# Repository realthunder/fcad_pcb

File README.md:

## FreeCAD scripts for PCB CAD/CAM & FEM

fcad_pcb is yet another way to improve ECAD/MCAD collaboration between
[FreeCAD](https://www.freecad.org/) and [KiCAD](https://kicad.org/).

The original purpose of these tools was to do **PCB milling in FreeCAD**. It can do much more now.:
* It can **generate gcode from kicad_pcb** directly without going through the gerber stage.
* It can let your **modify the PCB directly inside FC** (done already),
* and potentially export back to kicad_pcb (partially done).
* and finally it can **generate solid tracks, pads and plated drills to enable FEM and thermal analysis** on KiCad pcb boards.

## Installation

The fcad_pcb macro is written in Python and requires **FreeCAD 0.17** or later to work properly.

1. Clone this repo into your freecad macro directory. To check what the default path of your macro directory is go to dropdown `Macro` > `Macros..` and find the path in the field User macros location
    ```bash
    cd <path/to/your/macros/directory>
    git clone https://github.com/realthunder/fcad_pcb/
    ```
2. Enter the locally cloned repository
    ```bash
    cd fcad_pcb/
    ``` 
3. Download the repository submodules
    ```python
    git submodule update --init --recursive
    ```
4. Restart FreeCAD

## Usage

At this time fcad is usable through the [FreeCAD python console](https://wiki.freecad.org/Python_console). 

* Start FreeCAD,
* Launch the python console
  Enable through the `View > Panels > Python Console` dropdown menu
* Invoke the python `import` command to load fcad_pcb:
  ```python
  from fcad_pcb import kicad
  ```
**Result:** you are now ready to use fcad_pcb. 

#### Generating copper layers

```python
from fcad_pcb import kicad
pcb = kicad.KicadFcad(<full_path_to_your_kicad_pcb_file>)
pcb.makeCoppers()
```

**Note:** the file path syntax should be one of the following:
  ```python
  pcb = kicad.KicadFcad('C:/Users/fooDesktop/MyProject/MyPCBfilekicad_pcb')
  ```

  Alternatively if you don't want to replace backslashes for a Windows system:
  
  ```python
  pcb = kicad.KicadFcad(r'C:\Users\foo\Desktop\MyProject\MyPCBfile.kicad_pcb')`
  ```

#### Generating copper layers / pads / drills + ready for FEM workbench

Generate these full solid objects ready to for the FEM workbench

  ```python
  from fcad_pcb import kicad
  pcb = kicad.KicadFcad(<full_path_to_your_kicad_pcb_file>)
  pcb.make(copper_thickness=0.035, board_thickness=1.53, combo=False, fuseCoppers=True )
  #
  # NOTE: KiCAD 5.99 and later added possibility to specify per layer thickness including
  #       dielectric layers. You are no longer required to explicitly supply thickness
  #       parameters in any of the function calls as shown above.
  ```

#### Supply copper thickness per layer, pass a `dictionary` instead.

Use either **`integer`** or **`layer name`**
- **`integer`** (0~31, `0` being the front and `31` the back)
- **`layer name`** for key.
  **Note:** key `None` can be used for default thickness.

  ```python
  pcb.make(copper_thickness={None:0.05, 0:0.04, 'B.Cu':0.09},
           board_thickness=1.53, combo=False, fuseCoppers=True)
  #
  # NOTE: KiCAD 5.99 and later added possibility to specify per layer thickness
  #       including dielectric layers. You are no longer required to explicitly
  #       supply thickness parameters in any of the function calls as shown above.
  ```

#### Generating a single copper layer

```python
pcb.setLayer('F.Cu')
pcb.makeCopper()
```

#### <a name="net-filter"/>Filtering by net name</a>

For local nets you have to specify full hierarchical name

  ```python
  pcb.setNetFilter('GND')
  pcb.makeCopper()

  pcb.setNetFilter('GND','VCC')
  pcb.makeCopper()
  ```

#### Shape without intermediate document objects
In case you only want the shape without any intermediate document objects

  ```python
  from fcad_pcb import kicad
  pcb = kicad.KicadFcad(<full_path_to_your_kicad_pcb_file>, add_feature=False)

  # Or, you can set the parameter later
  pcb.add_feature = False

  # All the above makeXXX() calls now returns a shape without creating any features
  # For example, if you want the complete fused copper layers.
  # Note: 'thickness' can be a dictionary for per layer thickness
  coppers = pcb.makeCoppers(shape_type='solid', holes=True, fuse=True)
  Part.show(coppers)
  ```

  **Note:** that there is a **sample board** to play with inside this repo: [test.kicad_pcb](kicad_parser/test.kicad_pcb)

## Screenshots

#### FEM of tracks and drills

#### Full PCB in FreeCAD

#### PCB for milling

#### FEM of tracks and drills

### Requirements

`FreeCAD >= v0.17`

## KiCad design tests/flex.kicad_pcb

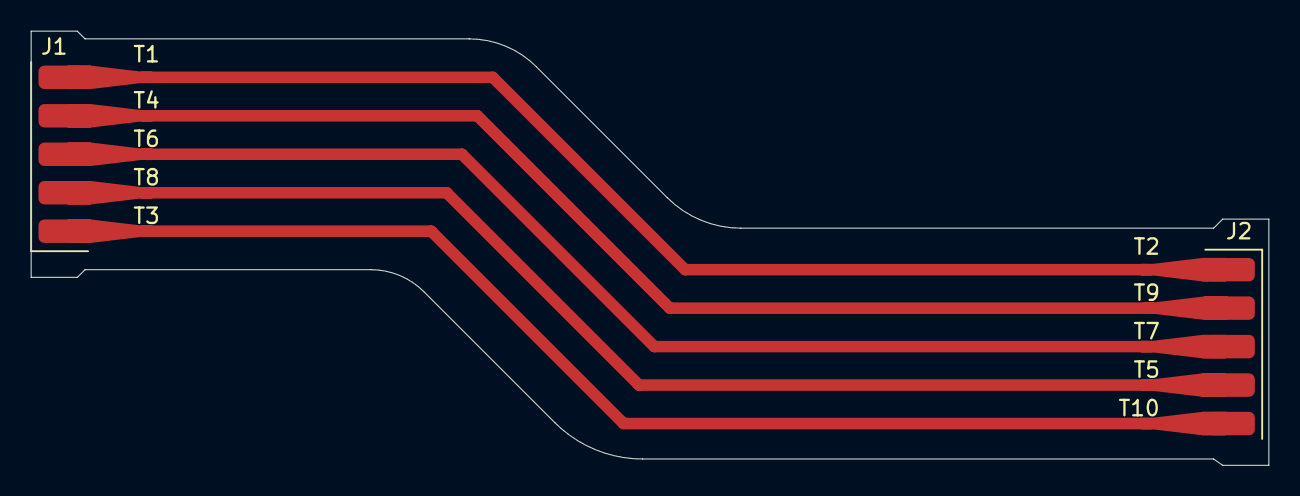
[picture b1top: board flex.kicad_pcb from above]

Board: 2 copper layers, 80.4 x 28.2 mm, 12 parts (0 on the bottom side), 5 nets.

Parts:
J1, J2: HEADER_5; flat-5p
T1, T2, T3, T4, T5, T6, T7, T8, T9, T10: TAPER; uwT0.75_0.75_1.52_1.52_4.00

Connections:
unnamed: J1.1, J2.5, T3.1, T10.1
unnamed: J1.2, J2.4, T5.1, T8.1
unnamed: J1.3, J2.3, T6.1, T7.1
unnamed: J1.4, J2.2, T4.1, T9.1
unnamed: J1.5, J2.1, T1.1, T2.1

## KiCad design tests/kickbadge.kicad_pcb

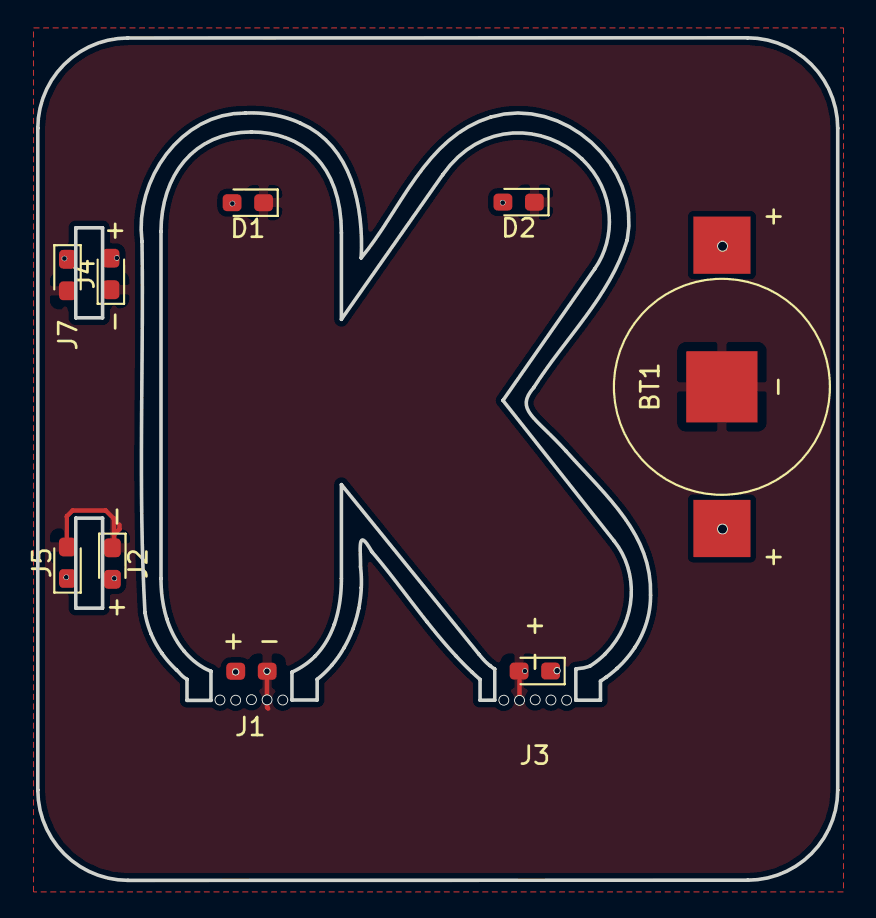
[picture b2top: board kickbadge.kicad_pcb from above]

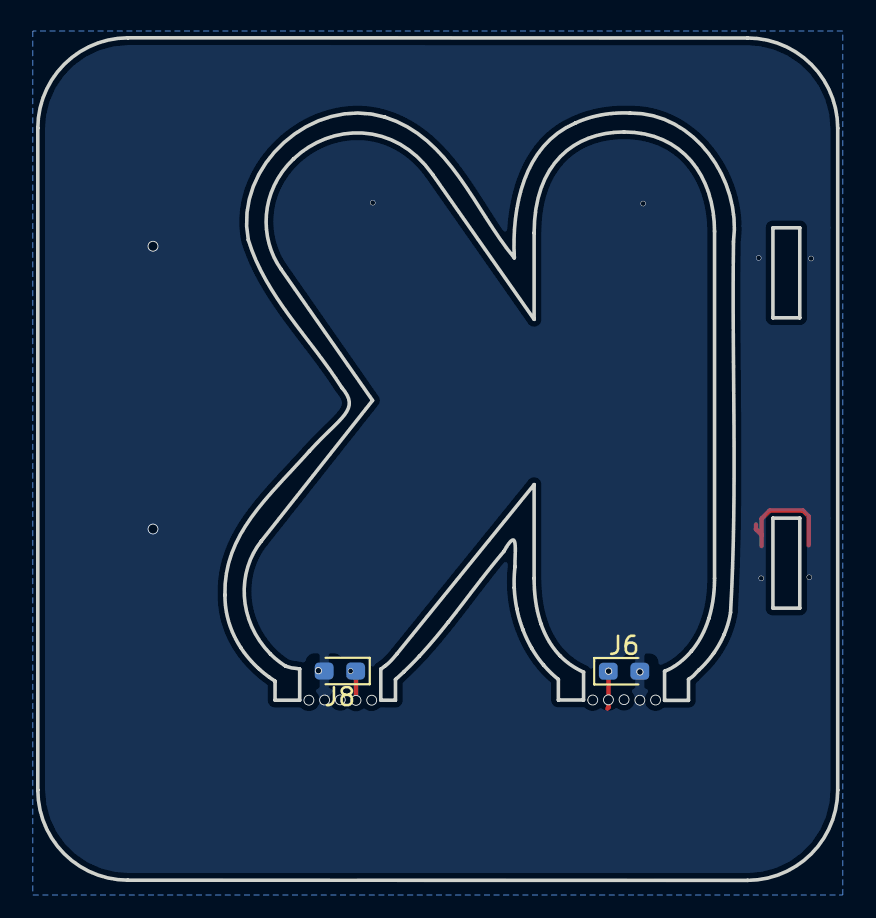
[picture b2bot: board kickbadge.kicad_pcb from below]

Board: 2 copper layers, 44.4 x 46.8 mm, 11 parts (2 on the bottom side), 2 nets.

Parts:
BT1: Battery; Keystone-3000
D1, D2: LED; LED_0603_1608Metric_Pad1.05x0.95mm_HandSolder
J1, J2, J3, J4: Conn_01x02_Male; connector_01x02
J5: FT-L; connector_01x02
J6: K-L-B; connector_01x02
J7: FT; connector_01x02
J8: K-R-B; connector_01x02

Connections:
GND: BT1.2, D1.1, D2.1, J1.2, J2.1, J3.2, J4.1, J5.2, J6.1, J7.2, J8.1
VCC: BT1.1, D1.2, D2.2, J1.1, J2.2, J3.1, J4.2, J5.1, J6.2, J7.1, J8.2

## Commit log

2017-01-05 Added kicad scripts
2017-01-09 PCB making almost done
2017-02-09 Major refactor using Path.Area
2017-02-09 Added fitView()
2017-03-24 Added timestamp to model cache
2017-06-11 skipping errors when finding Line through identical points
    reference kicad design to test
    https://github.com/FPGAwars/icezum/blob/master/src-kicad/icezum.kicad_pcb
2017-06-12 missing code after else: in previous commit
2017-07-09 Changed to use FC tag based logging
2017-07-09 Support fusing coppers solid with plated through holes
2018-03-31 added readme and screenshots
2018-04-30 Fix color on my fork of FC
2018-04-30 Fix copper fuse
2018-04-30 Support rounded rectangle pad
2018-05-01 Support custom pad with polyline
2018-05-01 Disable Area coplanar checking
2018-05-01 Fix bug when making shape without document objects
2018-05-01 Update kicad_parser sub module
2018-05-01 minor fix for mispelled code example
2018-05-01 Fix single line track making
2018-05-01 Auto enlarge NPTH holes before cutting
2018-05-01 Fix copper offset when not fusing
2018-05-02 Add hole_size_offset parameter
    This act as the default (0.0001 mm) hole size ajustement to deal with
    tolerance problem.
2018-05-02 Fix hole shape cache
2018-05-02 Add test cases
2018-10-08 Support Python3
    Fixes #10
2018-11-20 Fix kicad conf file reading
    Closes #12
2018-11-20 Fix kicad part path finding
    Closes #11
2019-03-25 Fix handling of reverse angle in makeArc()
    Fixes #13
2019-03-25 Fix propagation of fix_arc in makeBoard()
2019-03-26 Support filter by net name
    Closes #14
2019-03-26 Add info how netnames should be given
2019-05-04 Add support of gr_curve in Edge.cuts
    Closes #16
2019-05-04 Add gr_curve test board
2019-05-13 Change submodule url
2019-07-10 Support quoted layer names
    Closes #18
2019-07-30 Fix mistypes
2020-02-11 Add support for trapezoid pad
    Fixes #20
2020-02-11 Add support of chamfer pad
2020-02-11 Support pad shape offset
2020-02-12 Add 'via_bound' parameter for via simplication
    Closes #22
2020-02-12 Temporary fix of overlapping pads problem
    Fixes #21
2020-02-13 Fix trapezoid pad that collpase to triangle
    Related #20
2020-02-13 Add via_skip_hole parameter
    The parameter determines whether to skip via hole in case via_bound is
    set. This parameter is only effective when making fused copper
    Related #22
2020-02-14 Fix custom pad polygon orientation
2020-02-14 Add new parameters pad_inflate and zone_inflate
    For adding extra offset to close tiny holes due to tolerance issue
2020-03-09 Support more primitives in custom pad
2020-03-10 Support gr_circle primitive in pads and board
2020-04-14 Add support for blind vias
    Closes #23
2020-04-14 Support 'arc' type PCB trace
    Closes #24
2020-04-14 Add new parameter 'arc_fit_accuracy'
    To control Path.Area discretization and arc fit accuracy. Because of
    the small size of PCB features, the default value is set to 0.0005
    instead of the system default 0.01.
2020-04-15 Update kicad_parser submodule
    Related #23
2020-05-06 Fix layer filtering when making pads
    Fixes #25
2020-05-14 Support per layer copper thickness
2020-06-03 Modify readme
2020-07-07 Support gr_rect primitives
    Closes #26
2020-08-07 Fix zone layer filtering
2020-11-29 Support new kicad_pcb keyword 'footprint' as alias to 'module'
    Fixes #27
2020-11-30 Fix typo in _makeArea
    Typo change in _makeArea function of kicad.py.
2020-11-30 Update kicad_parser submodule
    Add 'fp_arc' sub key to footprint/module
    Related #27
2021-01-29 Fix zone inflating
    Related #30
2021-03-22 Fix missing fit_arcs option in makeTracks()
2021-03-22 Extension option 'combo' in make()
    Fuse the final output if combo > 1
2021-03-30 Parse KiCAD parameters both in JSON format and in the old INI format.
2021-04-23 Unquote net name
2021-04-23 Support edge cuts inside footprint
    Related #35
2021-04-27 Remove use of future module
2021-05-05 Allow via_skip_hole without via_bound
    Related #38
2021-06-17 Reset net filter when calling setNetFilter()
2021-07-22 Fix typos
2021-07-25 Update kicad_parser submodule
2021-09-24 Fix custom pad with user defined width (i.e. offset)
    Fixes #43
    @easyw
2021-09-24 Support fp shapes in pad
    Fixes #42
    @easyw
2021-09-26 Support stackup setup inside kicad_pcb
    Closes #41
    @sslupsky @veryLazyTom
2021-09-26 Fix _makeArea() error for single linear edge
    By always explicitly setting a workplane
    Related #42
2021-09-26 Fix makeBoard() with given thickness
    Related #42
2021-09-27 Fix copper layer order
2021-09-27 Fix line thickening
    Use 'Offset' instead of 'Thicken' parameter of Path.Area
2021-09-27 Do not use Link for extra dielectric layers
    For backward compatibility of older FreeCAD
2021-09-27 Fix zone on F&B.Cu
    Fixes #44
    @easyw
2021-09-27 Add new test file
2021-09-27 Fix zone layer filtering
    Related #44
2021-09-27 Fix board thickness calculation from stakup
    @easyw
2021-09-28 Fix zone layer filtering backward compatibility
    Fixes #45
    @easyw
2021-09-30 Fix making objects without hole
    Fixes #46
    @easyw
2021-10-27 Fix KiCad website link in Readme
    Fixes #47
    @Gasman2014
2021-10-28 Fix cases where there is no hole
2021-10-28 Support making arc with three points
    Closes #48
    @easyw
2021-11-28 Update kicad_parser module
2021-11-29 Use sexp_parser.unquote()
2021-11-29 Support loading kicad_mod
    If it is kicad_mod, the originally parsed file is stored in
    self.module, while self.pcb is a constructed skeleton kicad_pcb file
    that contains only one module. The board edge is derived from F.CrtYd
    or B.CrtYd.
    You can access module attributes like
    self.module.fp_line[0].width
2021-12-03 Added few things to the ReadMe that got me stucked when trying to use the macro for the first time.
2021-12-05 README: reformat markdown + refine + misc. fixes
2021-12-05 Fixed missed typo
2022-03-21 Expose KicadPCB.load(quote_no_parse)
2022-03-21 Fix typo + rename to README.md
2022-07-14 Fix parsing of kicad_pcb stackup
    Fixes #57
2022-07-16 Fix parsing of thickness field in stackup
    Related #58
2022-07-20 Fix handling of stackup layer with multiple sublayers
    Related #57
    @easyw
2022-07-21 Fix parsing sublayer thickness
2022-10-12 Support loading kicad_pcb file produced by KiCad Gerber Viewer
    Closes #60
2023-01-05 Disable new topo naming when making objects
2023-01-22 Turn off shape validation
2023-01-22 Fix handling of custom pad shape
    Related easyw/kicadStepUpMod#157
    Related #62
2023-01-22 Fix handling of custom pad with no polygon
    Fixes #62
    @AlejoPm03
2023-01-22 Lower some log level
2023-01-28 Support 'footprint' in kicad_mod
    Closes #63
    @easyw
2023-06-27 Fix KiCAD path finding
2023-06-29 Fix blind/buried vias problem due to incorrect layer offset
    Related #68
2023-06-29 Fix handling of topo naming
    Auto enable topo naming to combine colors in compound
2023-06-29 Add tests for blind/buried vias
2023-07-02 Fix missing blind/buried vias if there is no through hole via
    Related #68
2023-07-03 Support removing annular rings of unconnected vias
    Related #68
2023-07-29 Fix typo
    Related #68
2023-08-03 Handle exception when finding zone layer connections
    Related #68
2023-11-04 Fix KiCAD path finding
    Closes #69
2023-11-04 Change some log output
2024-02-04 Fix custom pad
    Fixes #65
    @easyw
2024-02-04 Fix missing argument in _makeWires()
2024-02-04 Fix quoted layer filtering
    Fixes #66
    @aa956
2024-02-05 Fix kicad_mod file parsing
    Fixes #64
    @easyw
2024-02-11 Support making castellated copper
    Related #67
2024-05-14 Update kicad.py to remove the extra " from the net names.
    sometimes the net names include " around the names. this migh cause issue with using setNetFilter.
2024-05-22 made pad location more robust
2024-05-22 made it to export the location of the pads to later find them in gmsh
2024-05-22 made few changes to the code
2024-05-23 made it more flexible
2024-08-29 Fix missing circular holes in Edge.Cuts
2024-11-12 Support stroke width
2024-11-19 Add parameter for file encoding
    Default to utf-8
2024-11-19 Fix board color for board with more than 2 layers
